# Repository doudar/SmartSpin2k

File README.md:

# You can visit us at [Facebook](https://www.facebook.com/groups/716297469953492/)
# Did you know there's a SmartSpin2k companion App?

Find the source code here! -> [SS2kConfigApp](https://github.com/doudar/SS2kConfigApp/tree/develop) 

You can get it from the Apple App Store here:
<div style="display: flex; flex-wrap: wrap;">

</div>

Or for Android devices: 
<div style="display: flex; flex-wrap: wrap;">

</div>

# About
SmartSpin2k is a DIY project that allows you to turn any spin bike into a smart trainer. With SmartSpin2k, you can connect your spin bike to Zwift, TrainerRoad, or other popular training apps. This allows you to control your bike's resistance automatically, track your performance, and compete with other riders online.

SmartSpin2k is easy to build and requires only a few simple tools. The [entire build process](https://github.com/doudar/SS2k-Hardware/blob/main/SS2kR3BuildingInstructions.pdf) can be completed in under an hour.

If you are looking for a way to turn your spin bike into a smart trainer, SmartSpin2k is the perfect solution. With its new features and improvements, SmartSpin2k rev 3 is the best version yet.

## Getting Started

To get started with SmartSpin2k, you will need the following:

* A spin bike with a resistance control knob.
* A 3D printer.
* A soldering iron and basic soldering skills.

Once you have these materials, you can follow the [these instructions](https://github.com/doudar/SS2k-Hardware/blob/main/SS2kR3BuildingInstructions.pdf) to build your own SmartSpin2k. If you'd prefer to buy a pre-assembled kit, we have them for sale at [SmartSpin2k.com](https://www.smartspin2k.com/purchase-kits) 

## Features

SmartSpin2k offers a number of features, including:

* Automatic incline resistance control: SmartSpin2k can automatically control your bike's resistance based on the resistance settings in your training app. This allows you to focus on your workout and not worry about adjusting the resistance yourself.
* SmartSpin2k ERG function is a great way to improve your cycling performance. It allows you to train at a consistent power output, which is essential for improving your speed and endurance. ERG stands for "electronic resistance control." It works by automatically adjusting the resistance on your bike based on the power output you set in your training app.
* Online competition: SmartSpin2k can connect to Zwift, TrainerRoad, and many other cycling apps allowing you to compete with other riders online. This is a great way to stay motivated and push yourself to new heights.
* Do you have a spin bike that doesn't output realistic or accurate power numbers? If so, you're not alone. Many spin bikes have inaccurate power meters that can make it difficult to track your progress and train effectively. With SmartSpin2k you can calibrate the power output of your spin bike. 

## Conclusion

SmartSpin2k is a great way to turn any spin bike into a smart trainer. With its new features and improvements, SmartSpin2k Rev 3 is the best version yet. If you are looking for a way to improve your indoor cycling experience, SmartSpin2k is the perfect solution.

### Documentation
Everything you need to know is in the [SS2K Wiki](https://github.com/doudar/SmartSpin2k/wiki)
Hardware files and build assets are in [SS2k-Hardware](https://github.com/doudar/SS2k-Hardware).

## Contributing
1. Install Microsoft Visual Code. https://code.visualstudio.com/
2. Install the **pioarduino IDE** extension (`pioarduino.pioarduino-ide`) recommended by this repository in Visual Studio Code.
3. Install Python https://www.python.org/downloads/
4. Install Pre-commit. https://pre-commit.com `py -m pip install pre-commit`
5. Follow any install warnings to add pre-commit to your path. 
6. Install pre-push git hooks: `pre-commit install --hook-type pre-push`
7. Open this project in the pioarduino IDE.

For command-line builds, use a Python virtual environment and run `python -m pip install -r requirements-ci.txt` from the repository root to install the same pinned pioarduino Core used by CI. CI uses Python 3.11. If that environment already has the upstream `platformio` package installed, uninstall it before installing pioarduino; the two packages share Python modules and command names.

pioarduino still uses `platformio.ini`, the `.platformio` tool directory, and the `pio` / `platformio` commands. Build with `pio run -e release` (classic ESP32) or `pio run -e S3release` (ESP32-S3), and run native tests with `pio test -e native`. See [AGENTS.md](AGENTS.md) for build and validation details.

## Important announcement for existing users
If you experience an issue after upgrading firmware, please follow these instructions in the Wiki. Flashing instructions are available [HERE.](https://github.com/doudar/SmartSpin2k/wiki/Loading-Software)

## Licensing
The hardware designs are licensed under the [CERN Open Hardware License Version 2 - Permissive license](https://github.com/doudar/SS2k-Hardware/blob/main/Hardware/LICENSE).
The software in this project is licensed under the [GNU GENERAL PUBLIC LICENSE Version 2, June 1991 license](LICENSE).

[_^^@eMadman's IC4 model_](https://github.com/doudar/SS2k-Hardware/tree/main/Hardware/V2%20-%20Through%20Hole/Direct%20Mount)

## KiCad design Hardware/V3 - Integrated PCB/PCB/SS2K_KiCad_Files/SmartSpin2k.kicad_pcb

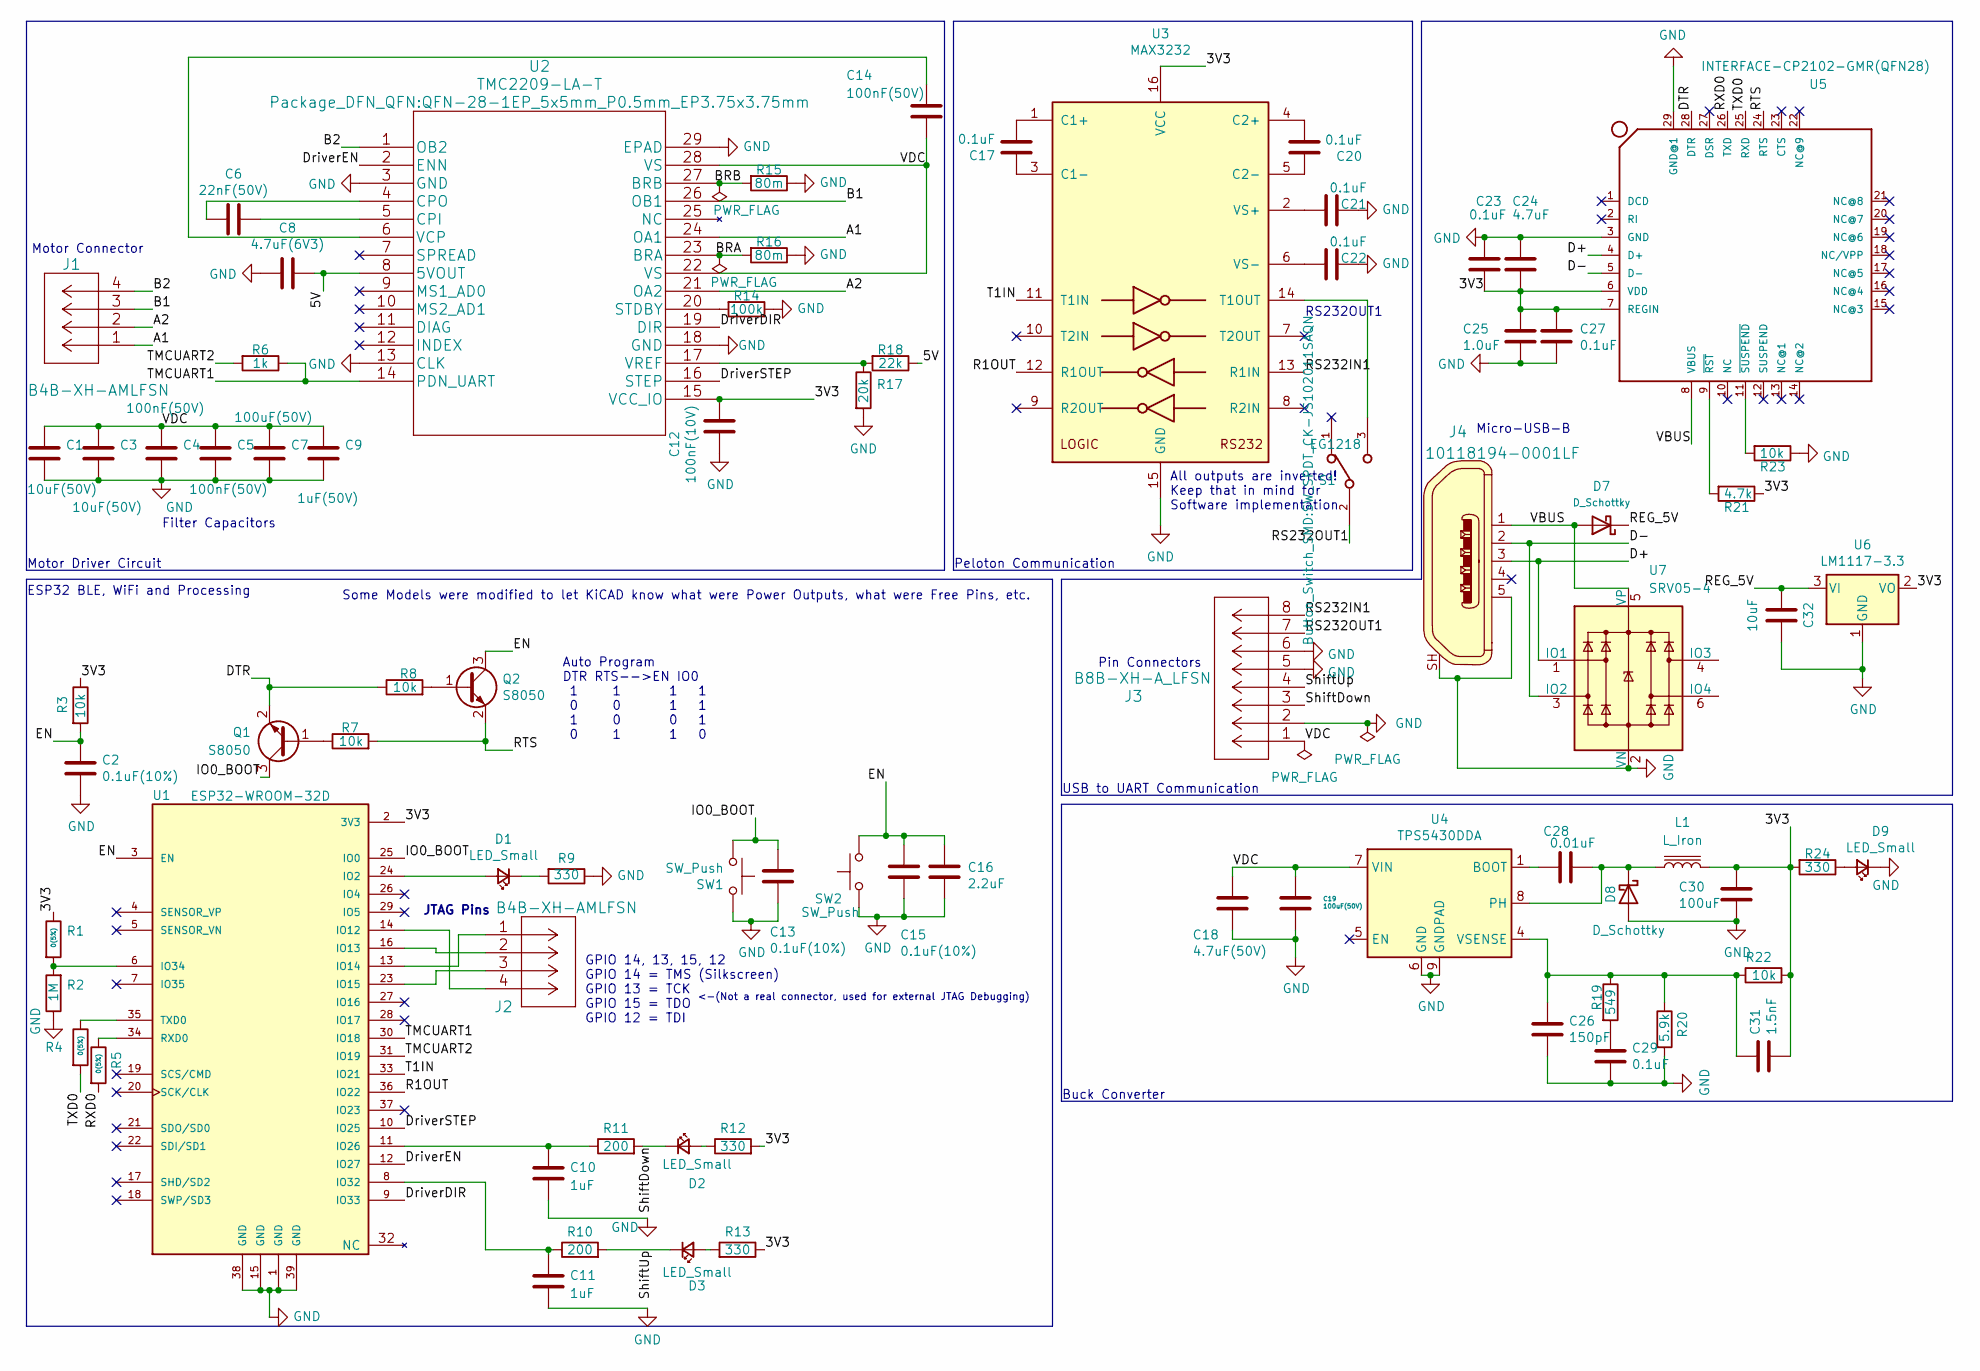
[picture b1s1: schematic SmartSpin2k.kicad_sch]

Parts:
C1: 10uF(50V); C_0805_2012Metric
C2, C13, C15: 0.1uF(10%); C_0402_1005Metric
C3: 10uF(50V); C_1206_3216Metric
C4, C5, C14: 100nF(50V); C_0805_2012Metric
C6: 22nF(50V); C_0805_2012Metric
C7, C19: 100uF(50V); CP_Elec_8x10
C8: 4.7uF(6V3); C_0805_2012Metric
C9: 1uF(50V); C_0603_1608Metric
C10, C11: 1uF; C_0603_1608Metric
C12: 100nF(10V); C_0805_2012Metric
C16: 2.2uF; C_0402_1005Metric
C17, C20, C21, C22, C23, C27, C29: 0.1uF; C_0402_1005Metric
C18: 4.7uF(50V); C_1206_3216Metric
C24: 4.7uF; C_0805_2012Metric
C25: 1.0uF; C_0805_2012Metric
C26: 150pF; C_0805_2012Metric
C28: 0.01uF; C_0805_2012Metric
C30: 100uF; C_1206_3216Metric
C31: 1.5nF; C_0805_2012Metric
C32: 10uF; C_0603_1608Metric
D1, D2, D3, D9: LED_Small; LED_0603_1608Metric
D7, D8: D_Schottky; D_SMA
J1, J2: B4B-XH-AMLFSN; JST_XH_B4B-XH-AM_1x04_P2.50mm_Vertical
J3: B8B-XH-A_LFSN; JST_XH_B8B-XH-AM_1x08_P2.50mm_Vertical
J4: 10118194-0001LF; USB_Micro_B_Female_10118194-0001LF; MPN 10118194-0001LF; Digi-Key_PN 609-4618-1-ND
L1: L_Iron; L_12x12mm_H8mm
Q1, Q2: S8050; SOT-23
R1, R4, R5: 0(5%); R_0402_1005Metric
R2: 1M; R_0402_1005Metric
R3, R7, R8, R22, R23: 10k; R_0402_1005Metric
R6: 1k; R_0402_1005Metric
R9, R12, R13, R24: 330; R_0402_1005Metric
R10, R11: 200; R_0402_1005Metric
R14: 100k; R_0402_1005Metric
R15, R16: 80m; R_1206_3216Metric
R17: 20k; R_0805_2012Metric
R18: 22k; R_0402_1005Metric
R19: 549; R_0402_1005Metric
R20: 5.9k; R_0603_1608Metric
R21: 4.7k; R_0402_1005Metric
S1: EG1218; SW_SPDT_CK-JS102011SAQN
SW1, SW2: SW_Push; SW_Push_SPST_NO_Alps_SKRK
U1: ESP32-WROOM-32D; ESP32-WROOM-32; PARTREV 1.9
U2: TMC2209-LA-T; QFN-28-1EP_5x5mm_P0.5mm_EP3.75x3.75mm
U3: MAX3232; MAX3232IPWR
U4: TPS5430DDA; SOIC-8-1EP_3.9x4.9mm_P1.27mm_EP2.514x3.2mm
U5: INTERFACE-CP2102-GMR(QFN28); QFN-28-1EP_5x5mm_P0.5mm_EP3.35x3.35mm; MPN CP2102-GMR
U6: LM1117-3.3; SOT-223-3_TabPin2
U7: SRV05-4; SOT-23-6

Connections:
/3V3: C12.1, C23.1, C24.2, C25.1, C27.1, C30.1, C31.2, L1.2, R1.1, R3.1, R12.2, R13.1, R21.1, R22.2, R24.2, U1.2 (3V3), U2.15 (VCC_IO), U3.16 (VCC), U5.6 (VDD), U5.7 (REGIN), U6.2 (VO)
/5V: C8.1, R18.1, U2.8 (5VOUT)
/A1: J1.1, U2.24 (OA1)
/A2: J1.2, U2.21 (OA2)
/B1: J1.3, U2.26 (OB1)
/B2: J1.4, U2.1 (OB2)
/BRA: R16.2, U2.23 (BRA)
/BRB: R15.2, U2.27 (BRB)
/D+: J4.3, U5.4 (D+), U7.1 (IO1)
/D-: J4.2, U5.5 (D-), U7.3 (IO2)
/DTR: Q1.2 (E), R8.1, U5.28 (DTR)
/DriverDIR: U1.9 (IO33), U2.19 (DIR)
/DriverEN: U1.12 (IO27), U2.2 (ENN)
/DriverSTEP: U1.10 (IO25), U2.16 (STEP)
/EN: C2.1, C15.1, C16.1, Q2.3 (C), R3.2, SW2.2, U1.3 (EN)
/IO0_BOOT: C13.1, Q1.3 (C), SW1.1, U1.25 (IO0)
/R1OUT: U1.36 (IO22), U3.12 (R1OUT)
/REG_5V: C32.2, D7.1 (K), U6.3 (VI)
/RS232IN1: J3.8, U3.13 (R1IN)
/RS232OUT1: J3.7, S1.2
/RTS: Q2.2 (E), R7.2, U5.24 (RTS)
/RXD0: R5.2, U5.26 (TXD)
/ShiftDown: D2.1 (K), J3.3, R11.2
/ShiftUp: D3.1 (K), J3.4, R10.2
/T1IN: U1.33 (IO21), U3.11 (T1IN)
/TMCUART1: R6.1, U1.30 (IO18), U2.14 (PDN_UART)
/TMCUART2: R6.2, U1.31 (IO19)
/TXD0: R4.2, U5.25 (RXD)
/VBUS: D7.2 (A), J4.1, U5.8 (VBUS), U7.5 (VP)
/VDC: C1.1, C3.1, C4.1, C5.1, C7.1, C9.1, C14.1, C18.1, C19.1, J3.1, U2.22 (VS), U2.28 (VS), U4.7 (VIN)
GND: C1.2, C2.2, C3.2, C4.2, C5.2, C7.2, C8.2, C9.2, C10.2, C11.2, C12.2, C13.2, C15.2, C16.2, C18.2, C19.2, C21.2, C22.2, C23.2, C24.1, C25.2, C26.2, C27.2, C29.2, C30.2, C32.1, D8.2 (A), D9.1 (K), J3.2, J3.5, J3.6, J4.5, J4.SH, R2.1, R9.1, R14.1, R15.1, R16.1, R17.2, R20.2, R23.1, SW1.2, SW2.1, U1.1 (GND), U1.15 (GND), U1.38 (GND), U1.39 (GND), U2.3 (GND), U2.13 (CLK), U2.18 (GND), U2.29 (EPAD), U3.15 (GND), U4.6 (GND), U4.9 (GNDPAD), U5.3 (GND), U5.29 (GND@1), U6.1 (GND), U7.2 (VN)
unnamed: C6.1, U2.5 (CPI)
unnamed: C6.2, U2.4 (CPO)
unnamed: C10.1, R11.1, U1.11 (IO26)
unnamed: C11.1, R10.1, U1.8 (IO32)
unnamed: C14.2, U2.6 (VCP)
unnamed: C17.1, U3.3 (C1-)
unnamed: C17.2, U3.1 (C1+)
unnamed: C20.1, U3.5 (C2-)
unnamed: C20.2, U3.4 (C2+)
unnamed: C21.1, U3.2 (VS+)
unnamed: C22.1, U3.6 (VS-)
unnamed: C26.1, C31.1, R19.1, R20.1, R22.1, U4.4 (VSENSE)
unnamed: C28.1, U4.1 (BOOT)
unnamed: C28.2, D8.1 (K), L1.1, U4.8 (PH)
unnamed: C29.1, R19.2
unnamed: D1.1 (K), R9.2
unnamed: D1.2 (A), U1.24 (IO2)
unnamed: D2.2 (A), R12.1
unnamed: D3.2 (A), R13.2
unnamed: D9.2 (A), R24.1
unnamed: J2.1, U1.13 (IO14)
unnamed: J2.2, U1.16 (IO13)
unnamed: J2.3, U1.23 (IO15)
unnamed: J2.4, U1.14 (IO12)
unnamed: Q1.1 (B), R7.1
unnamed: Q2.1 (B), R8.2
unnamed: R1.2, R2.2, U1.6 (IO34)
unnamed: R4.1, U1.35 (TXD0)
unnamed: R5.1, U1.34 (RXD0)
unnamed: R14.2, U2.20 (STDBY)
unnamed: R17.1, R18.2, U2.17 (VREF)
unnamed: R21.2, U5.9 (~RST)
unnamed: R23.2, U5.11 (~SUSPEND)
unnamed: S1.3, U3.14 (T1OUT)

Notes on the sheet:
Peloton Communication
JTAG Pins
Motor Connector
Buck Converter
ESP32 BLE, WiFi and Processing
RS232OUT1
USB to UART Communication
Pin Connectors
All outputs are inverted! Keep that in mind for Software implementation
<-(Not a real connector, used for external JTAG Debugging)
Some Models were modified to let KiCAD know what were Power Outputs, what were Free Pins, etc.
Auto Program DTR RTS-->EN IO0 1 1 1 1 0 0 1 1 1 0 0 1 0 1 1 0
GPIO 14, 13, 15, 12 GPIO 14 = TMS (Silkscreen) GPIO 13 = TCK GPIO 15 = TDO GPIO 12 = TDI
Motor Driver Circuit
Filter Capacitors
Micro-USB-B

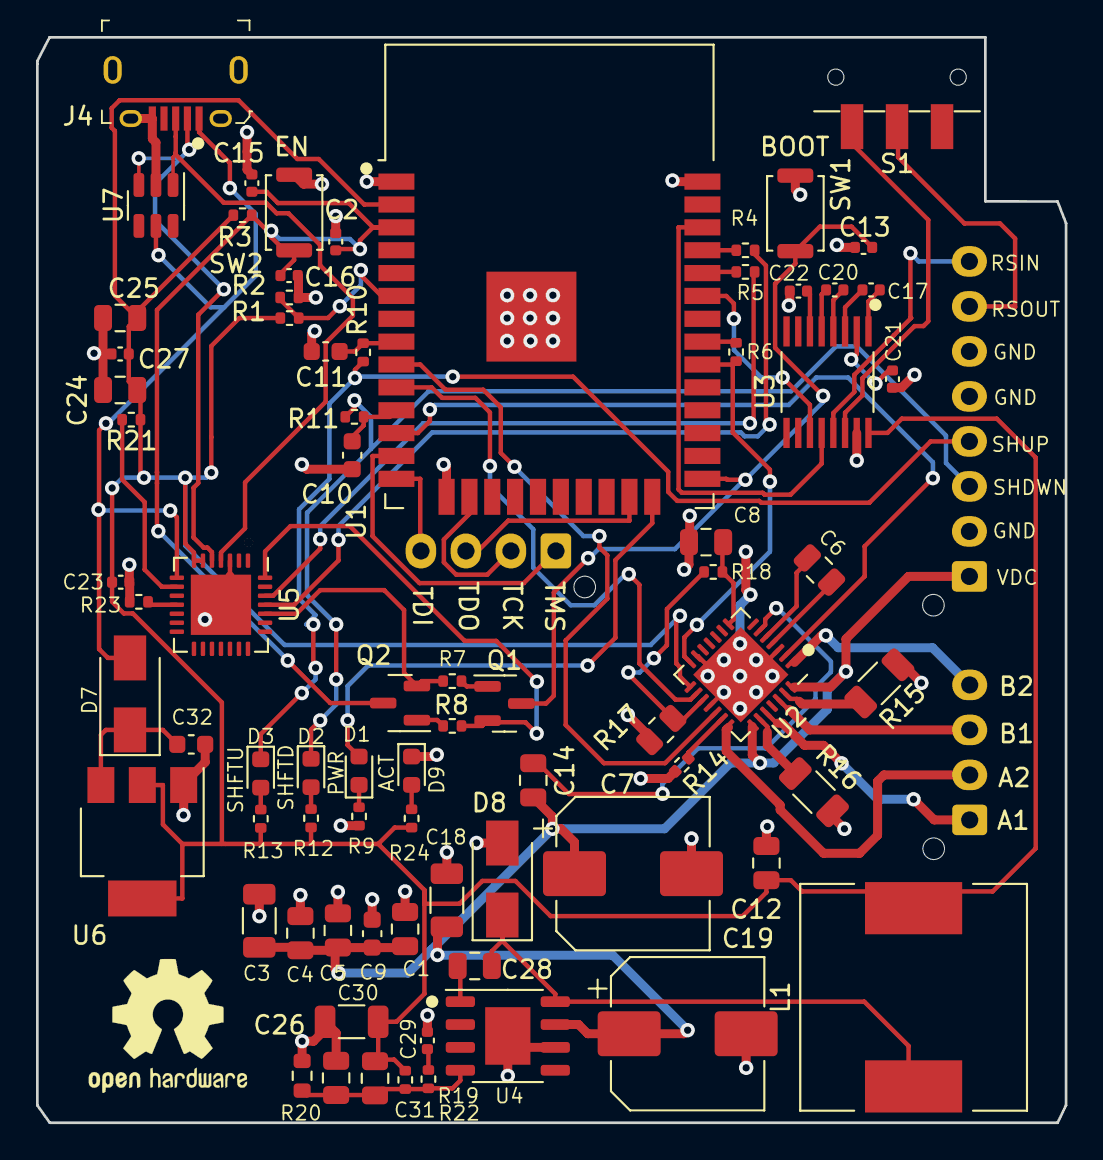
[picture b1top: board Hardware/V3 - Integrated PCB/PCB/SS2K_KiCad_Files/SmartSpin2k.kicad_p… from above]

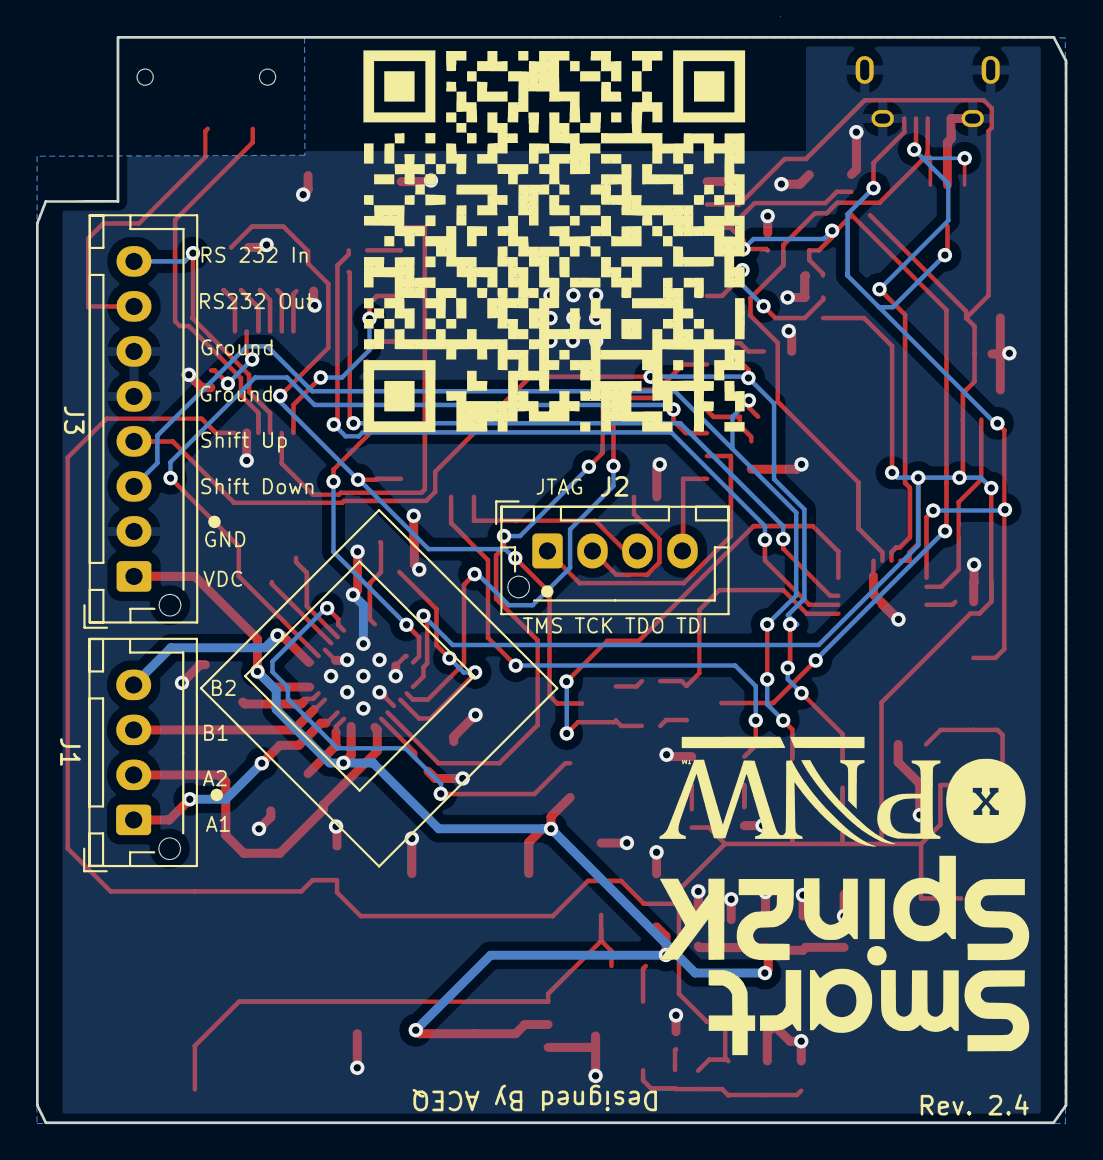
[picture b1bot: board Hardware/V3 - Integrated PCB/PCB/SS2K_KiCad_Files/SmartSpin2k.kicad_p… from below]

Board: 2 copper layers, 57.2 x 60.3 mm, 79 parts (3 on the bottom side), 65 nets.

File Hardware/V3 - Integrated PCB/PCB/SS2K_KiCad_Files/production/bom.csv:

Designator,Footprint,Quantity,Value,LCSC Part #
C1,C_0805_2012Metric,1,10uF(50V),
"C10, C11",C_0603_1608Metric,2,1uF,
C12,C_0805_2012Metric,1,100nF(10V),
"C13, C15, C2",C_0402_1005Metric,3,0.1uF(10%),
"C14, C4, C5",C_0805_2012Metric,3,100nF(50V),
C16,C_0402_1005Metric,1,2.2uF,
"C17, C20, C21, C22, C23, C27, C29",C_0402_1005Metric,7,0.1uF,
C18,C_1206_3216Metric,1,4.7uF(50V),
"C19, C7",CP_Elec_8x10,2,100uF(50V),
C24,C_0805_2012Metric,1,4.7uF,
C25,C_0805_2012Metric,1,1.0uF,
C26,C_0805_2012Metric,1,150pF,
C28,C_0805_2012Metric,1,0.01uF,
C3,C_1206_3216Metric,1,10uF(50V),
C30,C_1206_3216Metric,1,100uF,
C31,C_0805_2012Metric,1,1.5nF,
C32,C_0603_1608Metric,1,10uF,
C6,C_0805_2012Metric,1,22nF(50V),
C8,C_0805_2012Metric,1,4.7uF(6V3),
C9,C_0603_1608Metric,1,1uF(50V),
"D1, D2, D3, D9",LED_0603_1608Metric,4,LED_Small,
"D4, D5, D6",D_0603_1608Metric,3,D_TVS,
"D7, D8",D_SMA,2,D_Schottky,
"J1, J2",JST_XH_B4B-XH-AM_1x04_P2.50mm_Vertical,2,B4B-XH-AMLFSN,
J3,JST_XH_B8B-XH-AM_1x08_P2.50mm_Vertical,1,B8B-XH-A_LFSN,
J4,USB_Micro_B_Female_10118194-0001LF,1,10118194-0001LF,10118194-0001LF
L1,L_12x12mm_H8mm,1,L_Iron,
"Q1, Q2",SOT-23,2,S8050,
"R1, R4, R5",R_0402_1005Metric,3,0(5%),
"R10, R11",R_0402_1005Metric,2,200,
"R12, R13, R24, R9",R_0402_1005Metric,4,330,
R14,R_0402_1005Metric,1,100k,
"R15, R16",R_1206_3216Metric,2,80m,
R17,R_0805_2012Metric,1,20k,
R18,R_0402_1005Metric,1,22k,
R19,R_0402_1005Metric,1,549,
R2,R_0402_1005Metric,1,1M,
R20,R_0603_1608Metric,1,5.9k,
R21,R_0402_1005Metric,1,4.7k,
"R22, R23, R3, R7, R8",R_0402_1005Metric,5,10k,
R6,R_0402_1005Metric,1,1k,
S1,SW_SPDT_CK-JS102011SAQN,1,EG1218,
"SW1, SW2",SW_Push_SPST_NO_Alps_SKRK,2,SW_Push,
U1,ESP32-WROOM-32,1,ESP32-WROOM-32D,
U2,QFN-28-1EP_5x5mm_P0.5mm_EP3.75x3.75mm,1,TMC2209-LA-T,
U3,MAX3232IPWR,1,MAX3232,
U4,SOIC-8-1EP_3.9x4.9mm_P1.27mm_EP2.514x3.2mm,1,TPS5430DDA,
U5,QFN-28-1EP_5x5mm_P0.5mm_EP3.35x3.35mm,1,INTERFACE-CP2102-GMR(QFN28),CP2102-GMR
U6,SOT-223-3_TabPin2,1,LM1117-3.3,

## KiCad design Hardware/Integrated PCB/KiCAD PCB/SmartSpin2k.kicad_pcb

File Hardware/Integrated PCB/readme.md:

Working directory for the new PCB

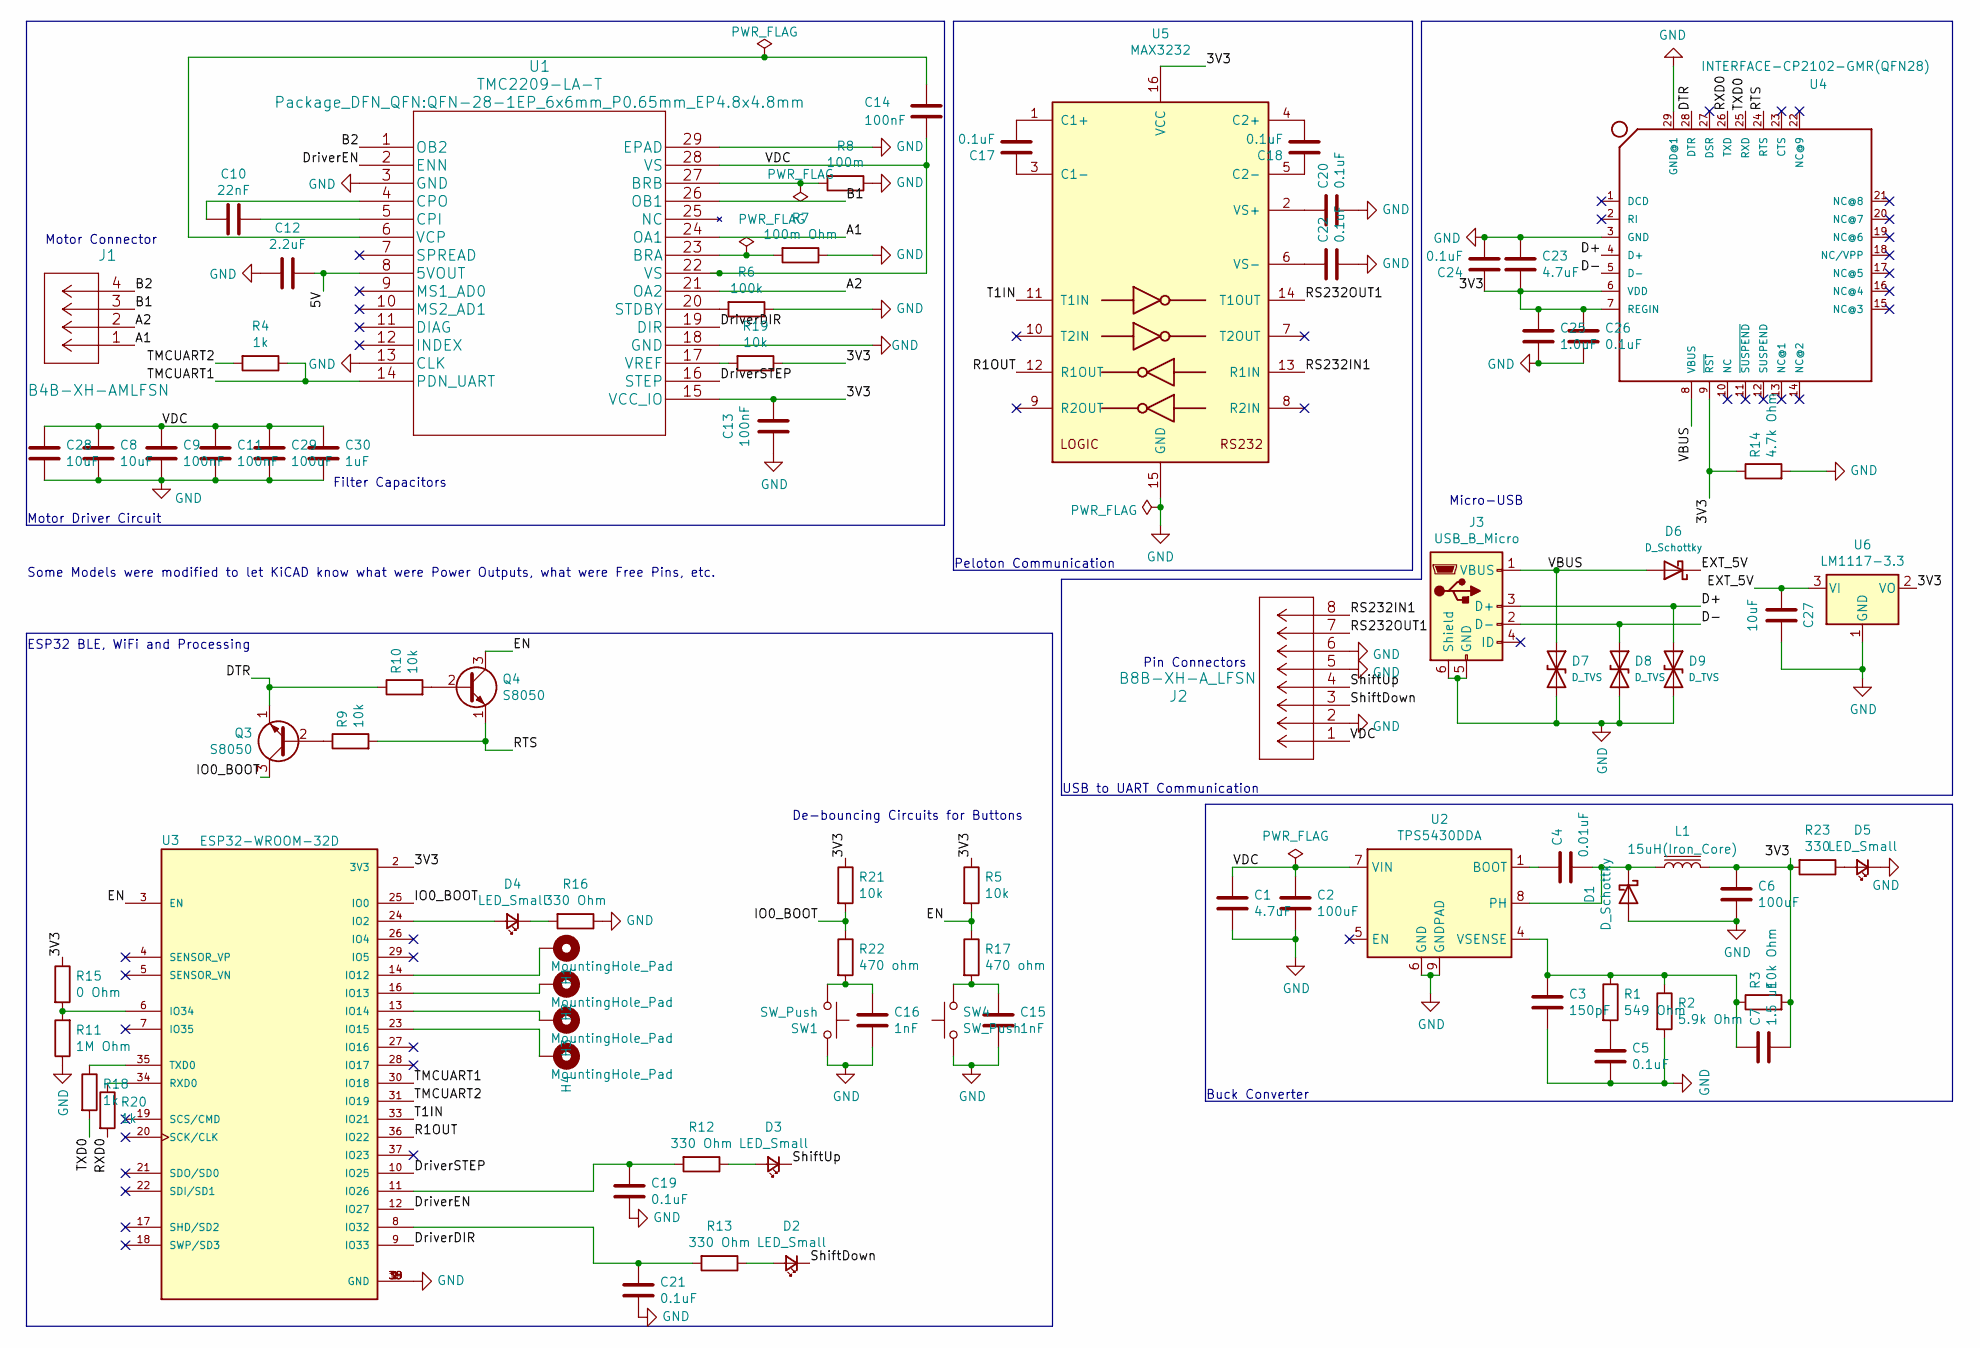
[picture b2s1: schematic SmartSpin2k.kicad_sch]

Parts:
C1, C23: 4.7uF; C_0805_2012Metric
C2, C6, C29: 100uF; C_0805_2012Metric
C3: 150pF; C_0805_2012Metric
C4: 0.01uF; C_0805_2012Metric
C5, C17, C18, C19, C20, C21, C22, C24, C26: 0.1uF; C_0402_1005Metric
C7: 1.5 uF; C_0805_2012Metric
C8: 10uF; C_0402_1005Metric
C9: 100nF; C_0805_2012Metric
C10: 22nF; C_0805_2012Metric
C11: 100nF; C_0603_1608Metric
C12: 2.2uF; C_0805_2012Metric
C13, C14: 100nF; C_0402_1005Metric
C15, C16: 1nF; C_0805_2012Metric
C25: 1.0uF; C_0805_2012Metric
C27: 10uF; C_0603_1608Metric
C28: 10uF; C_0805_2012Metric
C30: 1uF; C_0402_1005Metric
D1: D_Schottky; LED_0402_1005Metric
D2, D3, D4, D5: LED_Small; LED_0402_1005Metric
D6: D_Schottky; D_SOD-323
D7, D8, D9: D_TVS; D_SOD-523
H1, H2, H3, H4: MountingHole_Pad; TestPoint_THTPad_D1.0mm_Drill0.5mm
J1: B4B-XH-AMLFSN; JST_EH_B4B-EH-A_1x04_P2.50mm_Vertical
J2: B8B-XH-A_LFSN; JST_EH_B8B-EH-A_1x08_P2.50mm_Vertical
J3: USB_B_Micro; USB_Micro-B_Molex_47346-0001
L1: 15uH(Iron_Core); L_SXN_SMDRI127_150MT
Q3, Q4: S8050; SOT-23
R1: 549 Ohm; R_0402_1005Metric
R2: 5.9k Ohm; R_0402_1005Metric
R3: 10k Ohm; R_0402_1005Metric
R4, R18, R20: 1k; R_0402_1005Metric
R5, R9, R10, R19, R21: 10k; R_0402_1005Metric
R6: 100k; R_0402_1005Metric
R7: 100m Ohm; R_0402_1005Metric
R8: 100m; R_0402_1005Metric
R11: 1M Ohm; R_0402_1005Metric
R12, R13, R16: 330 Ohm; R_0402_1005Metric
R14: 4.7k Ohm; R_0402_1005Metric
R15: 0 Ohm; R_0402_1005Metric
R17, R22: 470 ohm; R_0402_1005Metric
R23: 330; R_0402_1005Metric
SW1, SW4: SW_Push; SW_Push_SPST_NO_Alps_SKRK
U1: TMC2209-LA-T; QFN-28-1EP_6x6mm_P0.65mm_EP4.8x4.8mm
U2: TPS5430DDA; SOIC-8-1EP_3.9x4.9mm_P1.27mm_EP2.514x3.2mm
U3: ESP32-WROOM-32D; ESP32-WROOM-32; PARTREV 1.9
U4: INTERFACE-CP2102-GMR(QFN28); QFN-28-1EP_5x5mm_P0.5mm_EP3.35x3.35mm_ThermalVias; MPN CP2102-GMR
U5: MAX3232; MAX3232IPWR
U6: LM1117-3.3; SOT-223-3_TabPin2

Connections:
/3V3: C6.1, C7.2, C13.1, C23.2, C24.1, C25.1, C26.1, L1.2, R3.2, R5.1, R14.1, R15.1, R19.1, R21.1, R23.2, U1.15 (VCC_IO), U3.2 (3V3), U4.6 (VDD), U4.7 (REGIN), U4.9 (~RST), U5.16 (VCC), U6.2 (VO)
/5V: C12.1, U1.8 (5VOUT)
/A1: J1.1, U1.24 (OA1)
/A2: J1.2, U1.21 (OA2)
/B1: J1.3, U1.26 (OB1)
/B2: J1.4, U1.1 (OB2)
/D+: D9.1 (A1), J3.3 (D+), U4.4 (D+)
/D-: D8.1 (A1), J3.2 (D-), U4.5 (D-)
/DTR: Q3.1 (E), R10.1, U4.28 (DTR)
/DriverDIR: U1.19 (DIR), U3.9 (IO33)
/DriverEN: U1.2 (ENN), U3.12 (IO27)
/DriverSTEP: U1.16 (STEP), U3.10 (IO25)
/EN: Q4.3 (C), R5.2, R17.1, U3.3 (EN)
/EXT_5V: C27.2, D6.1 (K), U6.3 (VI)
/IO0_BOOT: Q3.3 (C), R21.2, R22.1, U3.25 (IO0)
/R1OUT: U3.36 (IO22), U5.12 (R1OUT)
/RS232IN1: J2.8, U5.13 (R1IN)
/RS232OUT1: J2.7, U5.14 (T1OUT)
/RTS: Q4.1 (E), R9.2, U4.24 (RTS)
/RXD0: R20.2, U4.26 (TXD)
/ShiftDown: D2.1 (K), J2.3
/ShiftUp: D3.1 (K), J2.4
/T1IN: U3.33 (IO21), U5.11 (T1IN)
/TMCUART1: R4.1, U1.14 (PDN_UART), U3.30 (IO18)
/TMCUART2: R4.2, U3.31 (IO19)
/TXD0: R18.2, U4.25 (RXD)
/VBUS: D6.2 (A), D7.1 (A1), J3.1 (VBUS), U4.8 (VBUS)
/VDC: C1.1, C2.1, C8.1, C9.1, C11.1, C14.1, C28.1, C29.1, C30.1, J2.1, U1.22 (VS), U1.28 (VS), U2.7 (VIN)
GND: C1.2, C2.2, C3.2, C5.2, C6.2, C8.2, C9.2, C11.2, C12.2, C13.2, C15.2, C16.2, C19.2, C20.2, C21.2, C22.2, C23.1, C24.2, C25.2, C26.2, C27.1, C28.2, C29.2, C30.2, D1.2 (A), D5.1 (K), D7.2 (A2), D8.2 (A2), D9.2 (A2), J2.2, J2.5, J2.6, J3.5 (GND), J3.6 (Shield), R2.2, R6.1, R7.1, R8.1, R11.1, R14.2, R16.1, SW1.2, SW4.1, U1.3 (GND), U1.13 (CLK), U1.18 (GND), U1.29 (EPAD), U2.6 (GND), U2.9 (GNDPAD), U3.1 (GND), U3.15 (GND), U3.38 (GND), U3.39 (GND), U4.3 (GND), U4.29 (GND@1), U5.15 (GND), U6.1 (GND)
unnamed: C3.1, C7.1, R1.1, R2.1, R3.1, U2.4 (VSENSE)
unnamed: C4.1, U2.1 (BOOT)
unnamed: C4.2, D1.1 (K), L1.1, U2.8 (PH)
unnamed: C5.1, R1.2
unnamed: C10.1, U1.5 (CPI)
unnamed: C10.2, U1.4 (CPO)
unnamed: C14.2, U1.6 (VCP)
unnamed: C15.1, R17.2, SW4.2
unnamed: C16.1, R22.2, SW1.1
unnamed: C17.1, U5.3 (C1-)
unnamed: C17.2, U5.1 (C1+)
unnamed: C18.1, U5.5 (C2-)
unnamed: C18.2, U5.4 (C2+)
unnamed: C19.1, R12.2, U3.11 (IO26)
unnamed: C20.1, U5.2 (VS+)
unnamed: C21.1, R13.2, U3.8 (IO32)
unnamed: C22.1, U5.6 (VS-)
unnamed: D2.2 (A), R13.1
unnamed: D3.2 (A), R12.1
unnamed: D4.1 (K), R16.2
unnamed: D4.2 (A), U3.24 (IO2)
unnamed: D5.2 (A), R23.1
unnamed: H1.1, U3.14 (IO12)
unnamed: H2.1, U3.16 (IO13)
unnamed: H3.1, U3.13 (IO14)
unnamed: H4.1, U3.23 (IO15)
unnamed: Q3.2 (B), R9.1
unnamed: Q4.2 (B), R10.2
unnamed: R6.2, U1.20 (STDBY)
unnamed: R7.2, U1.23 (BRA)
unnamed: R8.2, U1.27 (BRB)
unnamed: R11.2, R15.2, U3.6 (IO34)
unnamed: R18.1, U3.35 (TXD0)
unnamed: R19.2, U1.17 (VREF)
unnamed: R20.1, U3.34 (RXD0)

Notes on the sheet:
Peloton Communication
Motor Connector
Buck Converter
De-bouncing Circuits for Buttons
ESP32 BLE, WiFi and Processing
USB to UART Communication
Pin Connectors
Some Models were modified to let KiCAD know what were Power Outputs, what were Free Pins, etc.
Motor Driver Circuit
Filter Capacitors
Micro-USB

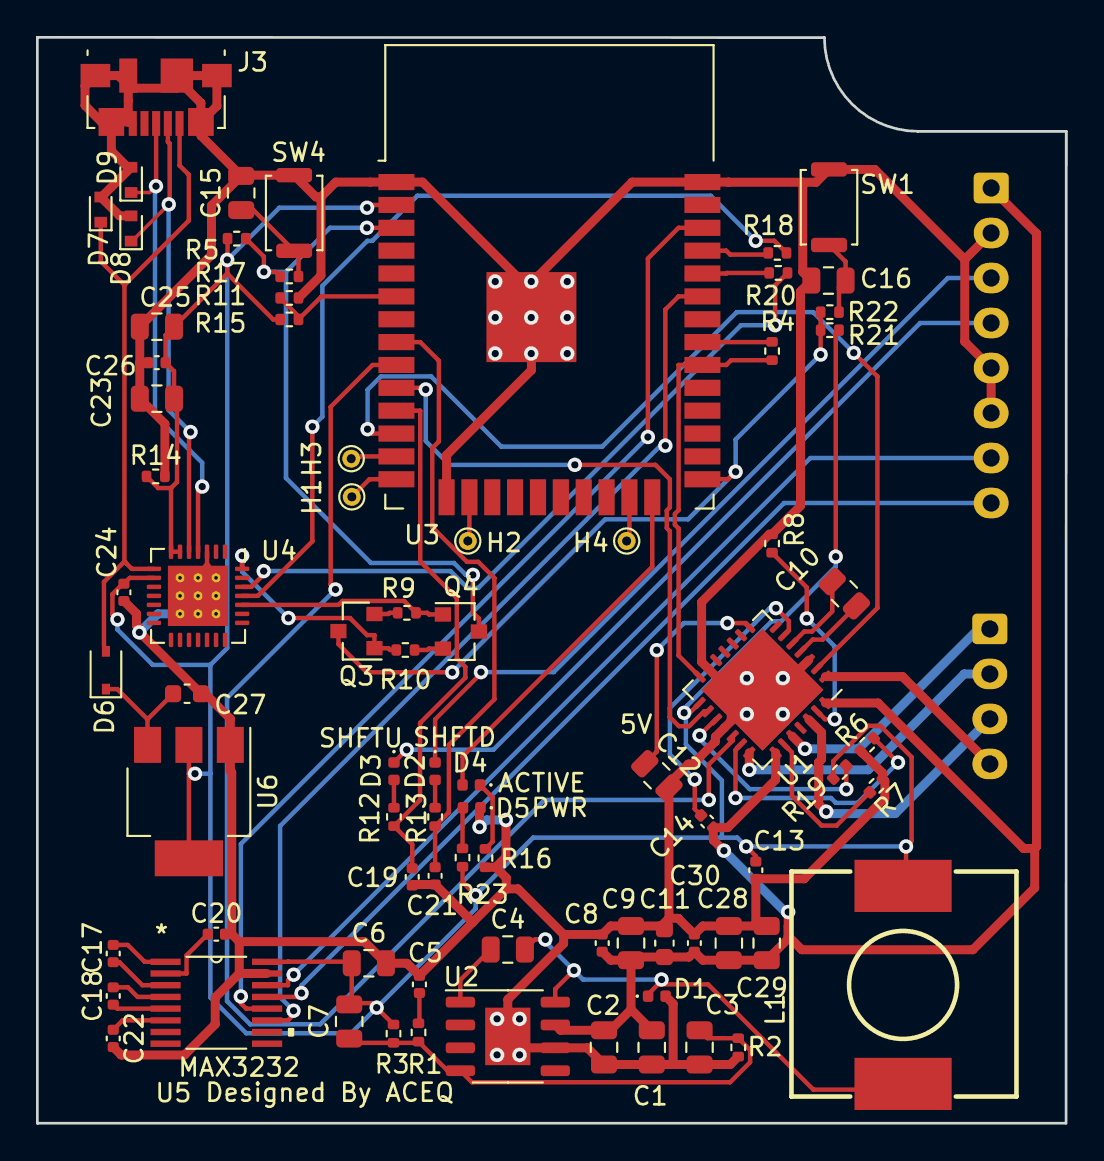
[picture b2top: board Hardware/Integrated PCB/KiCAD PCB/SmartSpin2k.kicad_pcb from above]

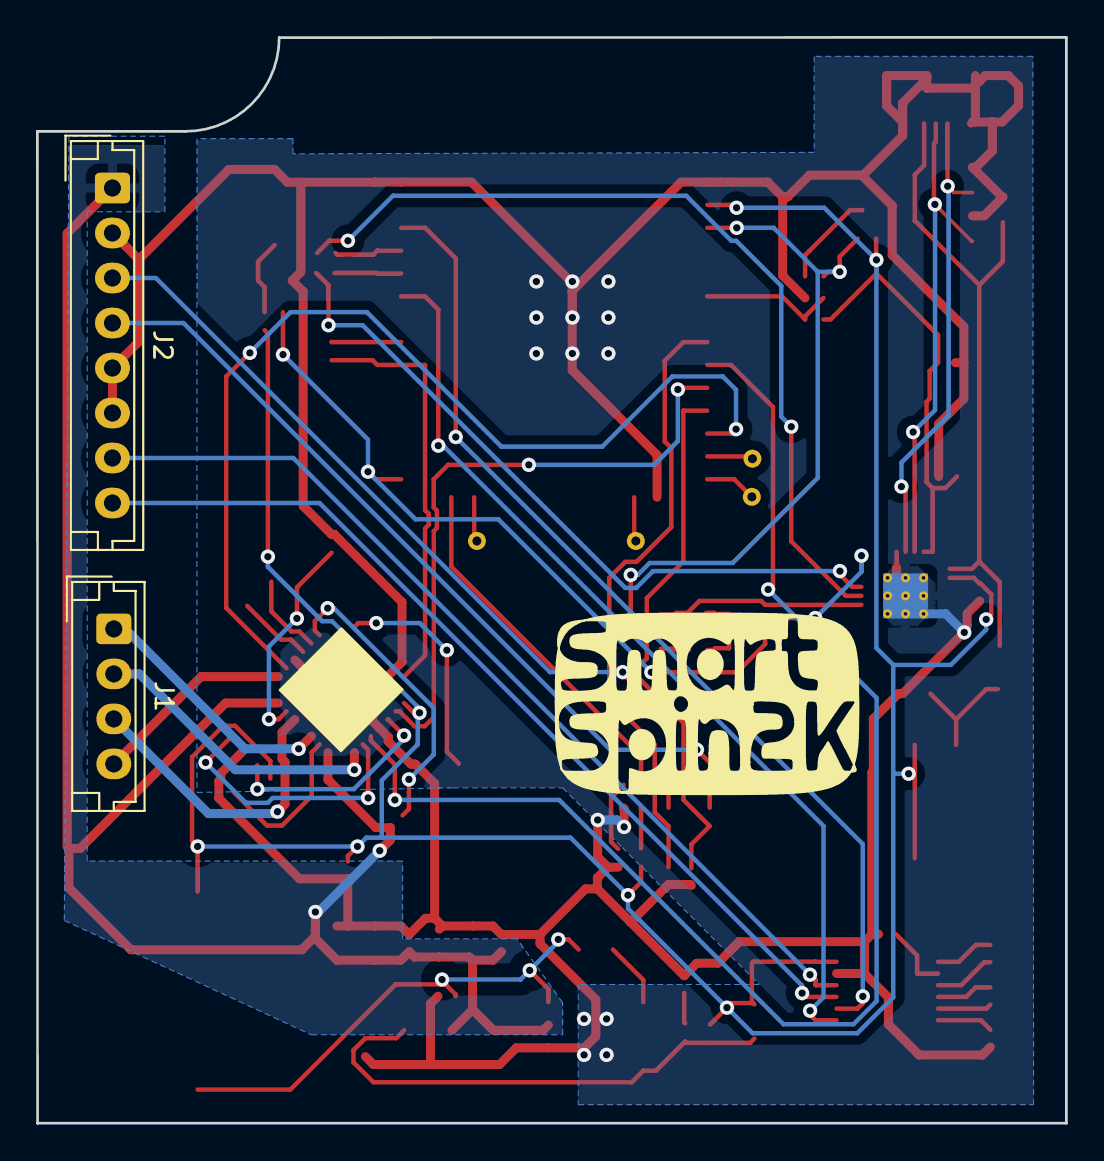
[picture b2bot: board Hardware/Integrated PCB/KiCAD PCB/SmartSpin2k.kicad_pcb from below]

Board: 2 copper layers, 57.2 x 60.3 mm, 80 parts (2 on the bottom side), 64 nets.

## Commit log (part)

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2025-11-18 Initial plan
2025-11-18 Fix misleading comments on resistance level conversion logic
2025-11-18 Added fallback to ERG while in resistance mode if we have no position information.
2025-11-18 comments and changelog updated.
2025-11-18 tweaked response in Resistance Mode
2025-11-20 Bump actions/checkout from 5 to 6
    Bumps [actions/checkout](https://github.com/actions/checkout) from 5 to 6.
    - [Release notes](https://github.com/actions/checkout/releases)
    - [Changelog](https://github.com/actions/checkout/blob/main/CHANGELOG.md)
    - [Commits](https://github.com/actions/checkout/compare/v5...v6)
    ---
    updated-dependencies:
2025-11-21 Fix spin down calibration by using indicate() for FTMS Control Point responses
    According to FTMS 1.0 spec, Control Point responses MUST use BLE indication (with acknowledgment) not notification (without acknowledgment). This fixes Zwift not recognizing spin down calibration com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
2025-11-21 Complete fix for spin down calibration issue - all checks passed
2025-11-21 Make Zwift happy during spin down by sending "stop pedaling" every 1 second
2025-11-24 Add power scalers for stepper hold and homing; update driver settings for improved stall detection
2025-11-24 Cadence needs to be >5 to initiate homing.
2025-11-24 added ftms homing user abort
2025-11-24 Minor text changes
2025-11-24 divide by 4 for resistance homing
2025-12-01 require cadence for 2 seconds before homing
2025-12-01 reduced delay to power down.
2025-12-02 More homing refinements
2025-12-03 Update links card
2025-12-11 Update CHANGELOG.md
    links card update
2025-12-11 Add custom characteristic command processing to WebSocket server
2025-12-11 Update documentation for WebSocket custom characteristic support
2025-12-11 Bump actions/cache from 4 to 5
    Bumps [actions/cache](https://github.com/actions/cache) from 4 to 5.
    - [Release notes](https://github.com/actions/cache/releases)
    - [Changelog](https://github.com/actions/cache/blob/main/RELEASES.md)
    - [Commits](https://github.com/actions/cache/compare/v4...v5)
    ---
    updated-dependencies:
2025-12-11 Send custom characteristic responses back through WebSocket
2025-12-11 added include for websocket appender
2025-12-17 Fix for Zwift On Android.
2025-12-18 IC4 reported HR won't override other HRM.
2025-12-18 Improved ERG response for homed tables.
2025-12-18 updated default settings
2025-12-25 - Removed >0 watts requirement to compute ERG.
2025-12-26 Add inactivity timeout config
2025-12-27 initial
2025-12-27 a little better
2025-12-28 almost there
2025-12-28 sync or async?
2025-12-28 bugfixes
2025-12-30 Working with Mark Roy to tune PID
2025-12-30 Use minutes instead of ms. Fix BLE
2025-12-30 Remove obsolete ms convertions
2025-12-31 - More ERG tweaks for Marc Roy.
2025-12-31 Revert "- More ERG tweaks for Marc Roy."
    This reverts commit ae53db69d04b5b06ce3ca93ab1a85a3d2c8b28c0.
2025-12-31 Merged Mark Roy with Marc Roy
2025-12-31 ERG being decoded correctly.
2025-12-31 Cleaning up
2025-12-31 - Added feed forward, disabled PowerTable for ERG lookup.
2026-01-01 Added tests and removal of duplicates in pt column.
2026-01-02 cleanup
2026-01-02 Set gear 8 after startup homing
2026-01-02 After startup homing, set gear 8.
2026-01-02 experimental lookup methods
2026-01-03 before removing monotonicity in favor of regression
2026-01-04 Ready to test again.
2026-01-04 added y-axis lock to testing
2026-01-04 Load power table if not yet loaded during session
2026-01-05 working great. needs cleanup.
2026-01-10 testing complete
2026-01-10 Switched inactivity timeout to 2F for compatibility with other recent changes.
2026-01-10 Fixed Case break from merge.
2026-01-10 Add BLE log streaming implementation
2026-01-10 Fix VLA stack overflow risk and revert unrelated dependencies.lock changes
2026-01-10 Change BLE_BLELogging characteristic code from 0x2F to 0x30
2026-01-10 Use existing BLE notification function instead of custom implementation
2026-01-11 hw test updates
2026-01-11 an example of why hardware should be seperate from software
2026-01-12 Updated case
2026-01-19 Increase BLE message size and silence MTU log
    Raised MAX_MESSAGE_SIZE in BleAppender from 180 to 500 to support larger BLE messages. Commented out the MTU update log in BLE_Server.cpp to reduce log verbosity.
2026-01-19 Fix ERG mode logic and improve power table validation; reset target incline on stop
2026-01-22 Include connected devices in BLE scan results
    Updated BLE scan logic to add connected devices to the found devices list when using the 'ANY' wildcard. Refactored scan end callback to remove redundant device aggregation, as devices are now added 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
2026-01-23 Sole Sb1200
2026-01-24 logging improvements
2026-01-31 fixed ERG sensitivity not being decimal in app
2026-01-31 Added Schwinn ACparts
2026-02-06 Removed initial connection params
2026-02-17 Update style.css
    accordion sections
2026-02-17 Update settings.html
    accordion sections
2026-02-17 Update CHANGELOG.md
    accordion sections
2026-03-01 updated connection params
2026-03-01 Add BLE appender and enhance logging for target positions
2026-03-01 Add Zwift custom BLE service and integrate virtual shifting functionality
2026-03-03 Controls almost working.
2026-03-03 Zwift rxing commands
2026-03-03 eliminated shifting feedback loop
2026-03-08 in progress
2026-03-08 Enhance DirCon service registration and write handling; remove deprecated methods
2026-03-08 Refactor BLE_Zwift_Service to improve session management and logging; remove handshake state handling
2026-03-09 back to Arduino BLE library
2026-03-09 Refactor BLE_Zwift_Service for improved code readability and consistency; adjust spacing and update service UUID references
2026-03-09 Thread safety and advertisement cleanup
2026-03-12 Enhance BLE_Zwift_Service with new payload handling methods and update command codes for trainer configuration
2026-03-12 Fixed some ZP errors
2026-03-18 updated countersink holes
2026-03-19 templated a couple functions
2026-03-19 Updated vents
2026-03-22 Case updates
2026-04-05 Update CA certificate for raw.githubusercontent.com
    - Replaced the outdated Sectigo certificate with the new Let's Encrypt R12 certificate.
    - Updated the last modified date to 2026-04-05.
2026-04-05 Debug working for S3
2026-04-11 [skip actions] changed readme to use the banner in hardware
2026-04-15 added openBikeControl
2026-04-21 working
2026-04-22 TMC driver work
2026-04-23 All go
2026-04-29 updated platformio.ini
2026-04-30 Better homing
2026-04-30 3 taps if first two don't agree
2026-04-30 Coolstep off during homing
2026-05-01 Garmin BLE changes
2026-05-02 fix(ble): restructure advertising and ensure spec compliance for Garmin compatibility
    - Restructured BLE advertising to prioritize the Cycling Power Service (CPS) UUID (0x1818) in the primary packet, mimicking commercial power meters to bypass strict Garmin discovery filters.
    - Added BLE Appearance (0x0484) to explicitly identify the device as a Cycling Power Sensor.
    - Moved the SmartSpin2k custom service UUID to the scan response to prevent advertising packet overflow and reduce noise for central scanners.
    - Updated the Cycling Power Measurement characteristic to NOTIFY only to comply with the Bluetooth CPP v1.1 specification.
    - Forced a public MAC address type to ensure stable pairing with
2026-05-02 updated changelog.md. Moved constants and definitions to header file. Code cleanup
2026-05-02 removed unused _closeToTarget
2026-05-02 added additional position update.
2026-05-02 formatting
2026-05-02 updated changelog
2026-05-02 fixed advertising
2026-05-03 Disabled OpenBikeControl and ZP (for now)
2026-05-04 Advertisement work
2026-05-04 removed hrm from advertisement
2026-05-04 updated build.yml
2026-05-06 [skip actions] Added better sunny 1805 pictures. Aligned sdkconfig.debug with release
2026-05-11 Guard networking when WiFi is disabled
    Agent-Logs-Url: https://github.com/doudar/SmartSpin2k/sessions/931c8bb8-5824-4b5e-b080-084036fdcd3d
2026-05-11 Deduplicate WiFi shutdown handling
    Agent-Logs-Url: https://github.com/doudar/SmartSpin2k/sessions/931c8bb8-5824-4b5e-b080-084036fdcd3d
2026-05-12 Move networking guards into main
    Agent-Logs-Url: https://github.com/doudar/SmartSpin2k/sessions/e759c192-9c60-4e03-be5d-88fac969b873
2026-05-12 Extract centralized network startup helper
    Agent-Logs-Url: https://github.com/doudar/SmartSpin2k/sessions/e759c192-9c60-4e03-be5d-88fac969b873
2026-05-12 Switch zero-watt ERG targets to sim mode
    Agent-Logs-Url: https://github.com/doudar/SmartSpin2k/sessions/33f20c65-9299-4587-81af-67f21f7b2a65
2026-05-12 Inline zero-watt ERG check
    Agent-Logs-Url: https://github.com/doudar/SmartSpin2k/sessions/760e2bb2-08f2-4f1e-b692-ec66f9a3726b
2026-05-22 sleep after 15min of inactivity after reboot
2026-05-23 changelog
2026-05-26 Added constants for namespace and keys and unwrapped the setup for readability.
2026-05-27 Add agent notes for SmartSpin2k firmware
2026-05-27 Simplified logic further. Moved flag from NVS to RTC memory.
2026-05-29 initial_commit
2026-06-18 build fix
2026-06-24 Bump dorny/paths-filter from 3 to 4
    Bumps [dorny/paths-filter](https://github.com/dorny/paths-filter) from 3 to 4.
    - [Release notes](https://github.com/dorny/paths-filter/releases)
    - [Changelog](https://github.com/dorny/paths-filter/blob/master/CHANGELOG.md)
    - [Commits](https://github.com/dorny/paths-filter/compare/v3...v4)
    ---
    updated-dependencies:
2026-06-24 Bump actions/upload-artifact from 5 to 7
    Bumps [actions/upload-artifact](https://github.com/actions/upload-artifact) from 5 to 7.
    - [Release notes](https://github.com/actions/upload-artifact/releases)
    - [Commits](https://github.com/actions/upload-artifact/compare/v5...v7)
    ---
    updated-dependencies:
    - dependency-name: actions/upload-artifact
2026-06-24 Bump dangoslen/changelog-enforcer from 3.6.1 to 3.7.0
    Bumps [dangoslen/changelog-enforcer](https://github.com/dangoslen/changelog-enforcer) from 3.6.1 to 3.7.0.
    - [Release notes](https://github.com/dangoslen/changelog-enforcer/releases)
    - [Changelog](https://github.com/dangoslen/changelog-enforcer/blob/main/CHANGELOG.md)
    - [Commits](https://github.com/dangoslen/changelog-enforcer/compare/v3.6.1...v3.7.0)
    ---
    updated-dependencies:
2026-06-24 Bump softprops/action-gh-release from 2 to 3
    Bumps [softprops/action-gh-release](https://github.com/softprops/action-gh-release) from 2 to 3.
    - [Release notes](https://github.com/softprops/action-gh-release/releases)
    - [Changelog](https://github.com/softprops/action-gh-release/blob/master/CHANGELOG.md)
    - [Commits](https://github.com/softprops/action-gh-release/compare/v2...v3)
    ---
    updated-dependencies:
2026-06-24 Bump actions/checkout from 6 to 7
    Bumps [actions/checkout](https://github.com/actions/checkout) from 6 to 7.
    - [Release notes](https://github.com/actions/checkout/releases)
    - [Changelog](https://github.com/actions/checkout/blob/main/CHANGELOG.md)
    - [Commits](https://github.com/actions/checkout/compare/v6...v7)
    ---
    updated-dependencies:
2026-06-24 Bump actions/download-artifact from 6 to 8
    Bumps [actions/download-artifact](https://github.com/actions/download-artifact) from 6 to 8.
    - [Release notes](https://github.com/actions/download-artifact/releases)
    - [Commits](https://github.com/actions/download-artifact/compare/v6...v8)
    ---
    updated-dependencies:
    - dependency-name: actions/download-artifact
2026-06-25 initial changes
    Custom BLE handling for Spinning CHrono Power
2026-06-25 feat: add ChronoData sensor support and implement BLE client task management

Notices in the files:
parts and their libraries:
Copyright 2021 Accelerated Designs. All rights reserved.
